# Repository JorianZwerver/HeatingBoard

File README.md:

# Heating Board PCB

PCB for MOD11 project. Measures current of four channels and can PWM each channel using a PMOS circuit. 

Schematic: [Schematic](Exports/HeatingBoard.pdf) \
Test results: [Results](Testing/2025_03_31_Test_Plan_Heating_Board_Execution.pdf) \
Test code for Arduino Uno: [Code](Testing/test_code.ino)

## Implementation

The board has 5 connectors:

| Connector ID | Description |
| ------------ | ----------- |
| J1 | Battery connector, is used for power. |
| J2 | Input interface for control, has a PWM pin for each group and the input for the 3V3 power. |
| J3 | I2C connector, contains SDA, SCL and GND. **However, the GND pin is broken and does not work.** |
| J4 | I2C connector, contains SDA, SCL and GND. |
| J5 | Output to the heating sleeve. Has four outputs and a GND that power the sleeve. |

### Current sensors

The current sensors communicate over the I2C bus. They need 3V3 power, but not battery power. The addresses are stated below:

| Channel number | Address (HEX) | Address (BIN) | Shunt resistor value (mOhm) |
| -------------- | ------------- | ------------- | --------------------- |
| 1 | 0x45 | 1000101 | 101   |
| 2 | 0x44 | 1000100 | 101.2 |
| 3 | 0x41 | 1000001 | 100.5 |
| 4 | 0x40 | 1000000 | 100.6 |

The datasheet can be found using this [link](https://www.ti.com/lit/ds/symlink/ina219.pdf?ts=1744040891714&ref_url=https%253A%252F%252Fwww.ti.com%252Fproduct%252FINA219). We have tested the current sensors in combination with a small load and encountered problems with the PWM, since the current sensor would sometimes measure the full current and sometimes zero current. To solve this, we increased the sample size and PWM frequency. This does mean that the sensor takes ~ 70 ms to get new data. We recommend the following settings:

- 12 bit shunt resolution
- 128 samples per measurement
- 2.5 kHz PWM frequency

We have found pretty accurate results using these settings, only deviating a couple of mW from the power supply. The testing code can be found [here](Testing/test_code.ino). The resistor values of the current shunts are shown in the table with the addresses for the current sensors.

### MOSFETs

During testing, we found that the duty cycle of the output voltage starts deviating from the input duty cycle for higher PWM frequencies. We have tested this for frequencies of 2.5, 5 and 10 kHz and we recommend 2.5 kHz. All results can be found in the [test report](Testing/2025_03_31_Test_Plan_Heating_Board_Execution.pdf).

## 3D Images

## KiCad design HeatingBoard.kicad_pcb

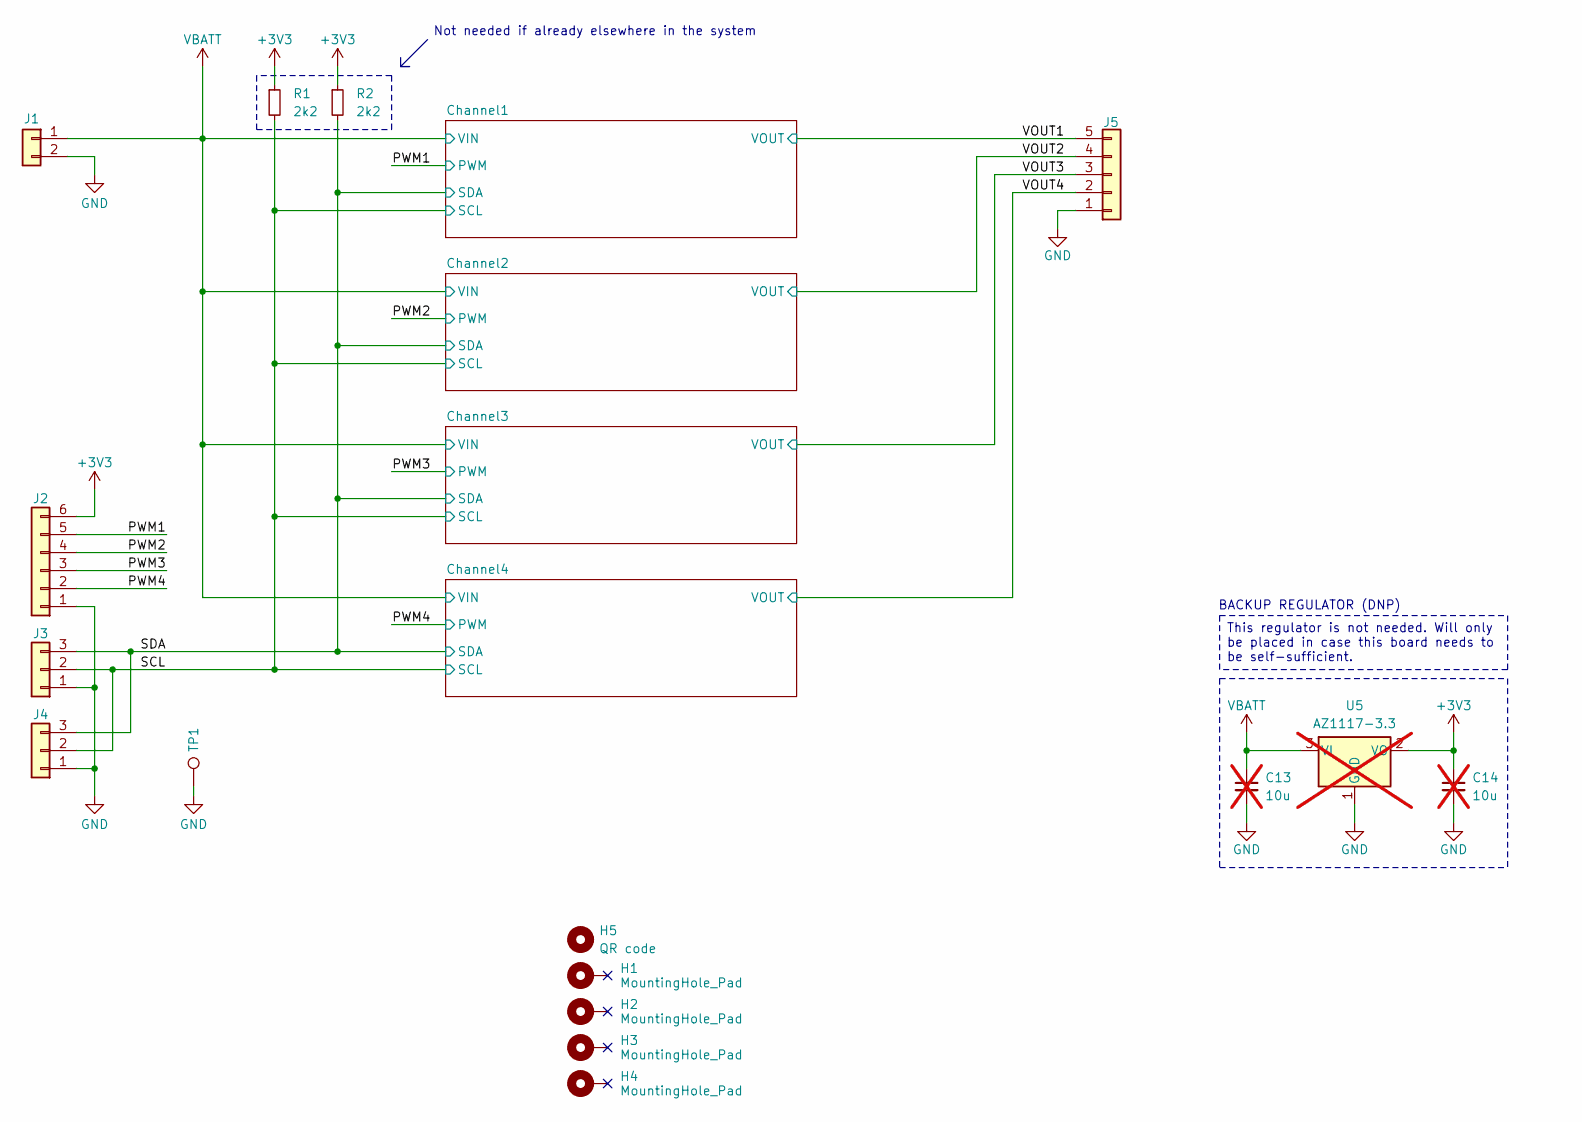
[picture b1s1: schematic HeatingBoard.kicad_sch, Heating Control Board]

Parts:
C13, C14: 10u; C_0805_2012Metric_Pad1.18x1.45mm_HandSolder; not fitted
H1, H2, H3, H4: MountingHole_Pad; MountingHole_3.2mm_M3_Pad
H5: QR code; QRcode
J1: Conn_01x02; PHOENIX_1935161
J2: Conn_01x06; PHOENIX_1935200
J3, J4: Conn_01x03; PHOENIX_1935174
J5: Conn_01x05; PHOENIX_1935190
R1, R2: 2k2; R_0603_1608Metric_Pad0.98x0.95mm_HandSolder
TP1: TestPoint; TestPoint_Plated_Hole_D5.0mm
U5: AZ1117-3.3; TO-220-3_Vertical; not fitted

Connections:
+3V3: C14.1, J2.6, R1.1, R2.1, U5.2 (VO); also elsewhere on the board
/PWM1: J2.5; also elsewhere on the board
/PWM2: J2.4; also elsewhere on the board
/PWM3: J2.3; also elsewhere on the board
/PWM4: J2.2; also elsewhere on the board
/SCL: J3.2, J4.2, R1.2; also elsewhere on the board
/SDA: J3.3, J4.3, R2.2; also elsewhere on the board
/VOUT1: J5.5; also elsewhere on the board
/VOUT2: J5.4; also elsewhere on the board
/VOUT3: J5.3; also elsewhere on the board
/VOUT4: J5.2; also elsewhere on the board
GND: C13.2, C14.2, J1.2, J2.1, J3.1, J4.1, J5.1, TP1.1, U5.1 (GND); also elsewhere on the board
VBATT: C13.1, J1.1, U5.3 (VI); also elsewhere on the board

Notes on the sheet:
BACKUP REGULATOR (DNP)
Not needed if already elsewhere in the system
This regulator is not needed. Will only be placed in case this board needs to be self-sufficient.

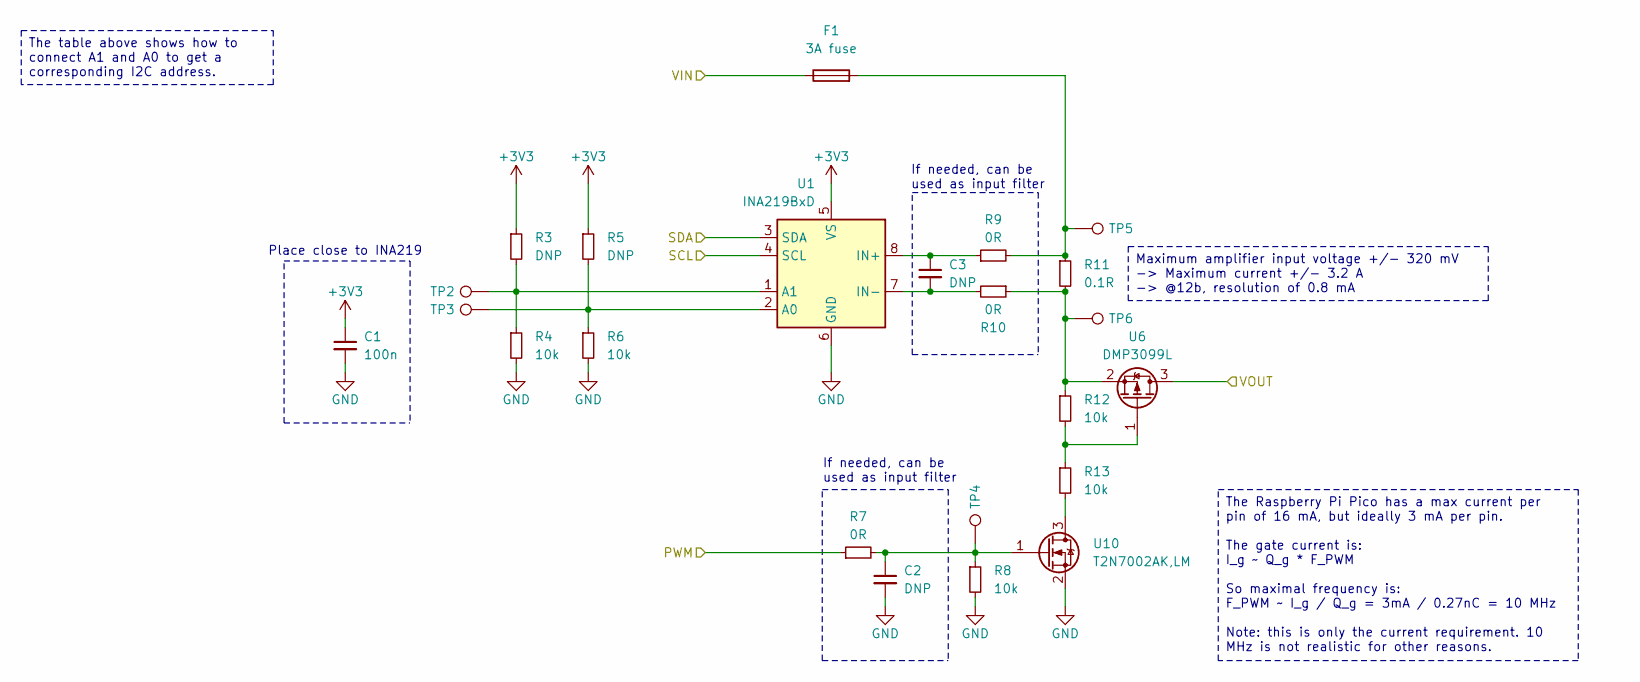
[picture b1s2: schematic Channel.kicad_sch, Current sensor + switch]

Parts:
C1: 100n; C_0603_1608Metric_Pad1.08x0.95mm_HandSolder
C2, C3: DNP; C_0603_1608Metric_Pad1.08x0.95mm_HandSolder
F1: 3A fuse; FUSE_0PTF0078P_LTF
R3, R5: DNP; R_0603_1608Metric_Pad0.98x0.95mm_HandSolder
R4, R6, R8, R12, R13: 10k; R_0603_1608Metric_Pad0.98x0.95mm_HandSolder
R7, R9, R10: 0R; R_0603_1608Metric_Pad0.98x0.95mm_HandSolder
R11: 0.1R; R_1206_3216Metric_Pad1.30x1.75mm_HandSolder
TP2, TP3, TP4, TP5, TP6: TestPoint; TestPoint_THTPad_1.0x1.0mm_Drill0.5mm
U1: INA219BxD; SOIC-8_3.9x4.9mm_P1.27mm
U6: DMP3099L; SOT-23
U10: T2N7002AK,LM; SOT-23

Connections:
+3V3: C1.1, R3.1, R5.1, U1.5 (VS); also elsewhere on the board
/PWM1: R7.1; also elsewhere on the board
/SCL: U1.4 (SCL); also elsewhere on the board
/SDA: U1.3 (SDA); also elsewhere on the board
/VOUT1: U6.3; also elsewhere on the board
GND: C1.2, C2.2, R4.2, R6.2, R8.2, U1.6 (GND), U10.2; also elsewhere on the board
unnamed: C2.1, R7.2, R8.1, TP4.1, U10.1
unnamed: F1.2, R9.2, R11.1, TP5.1
unnamed: R10.1, R11.2, R12.1, TP6.1, U6.2
unnamed: R12.2, R13.1, U6.1
unnamed: R13.2, U10.3
unnamed: R5.2, R6.1, TP3.1, U1.2 (A0)
unnamed: R3.2, R4.1, TP2.1, U1.1 (A1)
unnamed: C3.1, R9.1, U1.8 (IN+)
unnamed: C3.2, R10.2, U1.7 (IN-)
VBATT: F1.1; also elsewhere on the board

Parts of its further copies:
C4, C7, C10: 100n; C_0603_1608Metric_Pad1.08x0.95mm_HandSolder
C5, C6, C8, C9, C11, C12: DNP; C_0603_1608Metric_Pad1.08x0.95mm_HandSolder
F2, F3, F4: 3A fuse; FUSE_0PTF0078P_LTF
R14, R16, R25, R27, R36, R38: DNP; R_0603_1608Metric_Pad0.98x0.95mm_HandSolder
R15, R17, R19, R23, R24, R26, R28, R30, R34, R35, R37, R39, R41, R45, R46: 10k; R_0603_1608Metric_Pad0.98x0.95mm_HandSolder
R18, R20, R21, R29, R31, R32, R40, R42, R43: 0R; R_0603_1608Metric_Pad0.98x0.95mm_HandSolder
R22, R33, R44: 0.1R; R_1206_3216Metric_Pad1.30x1.75mm_HandSolder
TP7, TP8, TP9, TP10, TP11, TP12, TP13, TP14, TP15, TP16, TP17, TP18, TP19, TP20, TP21: TestPoint; TestPoint_THTPad_1.0x1.0mm_Drill0.5mm
U2, U3, U4: INA219BxD; SOIC-8_3.9x4.9mm_P1.27mm
U7, U8, U9: DMP3099L; SOT-23
U11, U12, U13: T2N7002AK,LM; SOT-23

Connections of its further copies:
+3V3: C4.1, C7.1, C10.1, R14.1, R16.1, R25.1, R27.1, R36.1, R38.1, U2.5 (VS), U3.5 (VS), U4.5 (VS); also elsewhere on the board
/PWM2: R18.1; also elsewhere on the board
/PWM3: R29.1; also elsewhere on the board
/PWM4: R40.1; also elsewhere on the board
/SCL: U2.4 (SCL), U3.4 (SCL), U4.4 (SCL); also elsewhere on the board
/SDA: U2.3 (SDA), U3.3 (SDA), U4.3 (SDA); also elsewhere on the board
/VOUT2: U7.3; also elsewhere on the board
/VOUT3: U8.3; also elsewhere on the board
/VOUT4: U9.3; also elsewhere on the board
GND: C4.2, C5.2, C7.2, C8.2, C10.2, C11.2, R15.2, R17.2, R19.2, R26.2, R28.2, R30.2, R37.2, R39.2, R41.2, U2.6 (GND), U3.6 (GND), U4.6 (GND), U11.2, U12.2, U13.2; also elsewhere on the board
unnamed: C5.1, R18.2, R19.1, TP9.1, U11.1
unnamed: C8.1, R29.2, R30.1, TP14.1, U12.1
unnamed: C11.1, R40.2, R41.1, TP19.1, U13.1
unnamed: F2.2, R20.2, R22.1, TP10.1
unnamed: F3.2, R31.2, R33.1, TP15.1
unnamed: F4.2, R42.2, R44.1, TP20.1
unnamed: R21.1, R22.2, R23.1, TP11.1, U7.2
unnamed: R23.2, R24.1, U7.1
unnamed: R24.2, U11.3
unnamed: R32.1, R33.2, R34.1, TP16.1, U8.2
unnamed: R34.2, R35.1, U8.1
unnamed: R35.2, U12.3
unnamed: R43.1, R44.2, R45.1, TP21.1, U9.2
unnamed: R45.2, R46.1, U9.1
unnamed: R46.2, U13.3
unnamed: R16.2, R17.1, TP8.1, U2.2 (A0)
unnamed: R14.2, R15.1, TP7.1, U2.1 (A1)
unnamed: C6.1, R20.1, U2.8 (IN+)
unnamed: C6.2, R21.2, U2.7 (IN-)
unnamed: R27.2, R28.1, TP13.1, U3.2 (A0)
unnamed: R25.2, R26.1, TP12.1, U3.1 (A1)
unnamed: C9.1, R31.1, U3.8 (IN+)
unnamed: C9.2, R32.2, U3.7 (IN-)
unnamed: R38.2, R39.1, TP18.1, U4.2 (A0)
unnamed: R36.2, R37.1, TP17.1, U4.1 (A1)
unnamed: C12.1, R42.1, U4.8 (IN+)
unnamed: C12.2, R43.2, U4.7 (IN-)
VBATT: F2.1, F3.1, F4.1; also elsewhere on the board

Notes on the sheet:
Place close to INA219
If needed, can be used as input filter
Maximum amplifier input voltage +/- 320 mV -> Maximum current +/- 3.2 A -> @12b, resolution of 0.8 mA
The Raspberry Pi Pico has a max current per pin of 16 mA, but ideally 3 mA per pin. The gate current is: I_g ~ Q_g * F_PWM So maximal frequency is: F_PWM ~ I_g / Q_g = 3mA / 0.27nC = 10 MHz Note: this is only the current requirement. 10 MHz is not realistic for other reasons.
The table above shows how to connect A1 and A0 to get a corresponding I2C address.

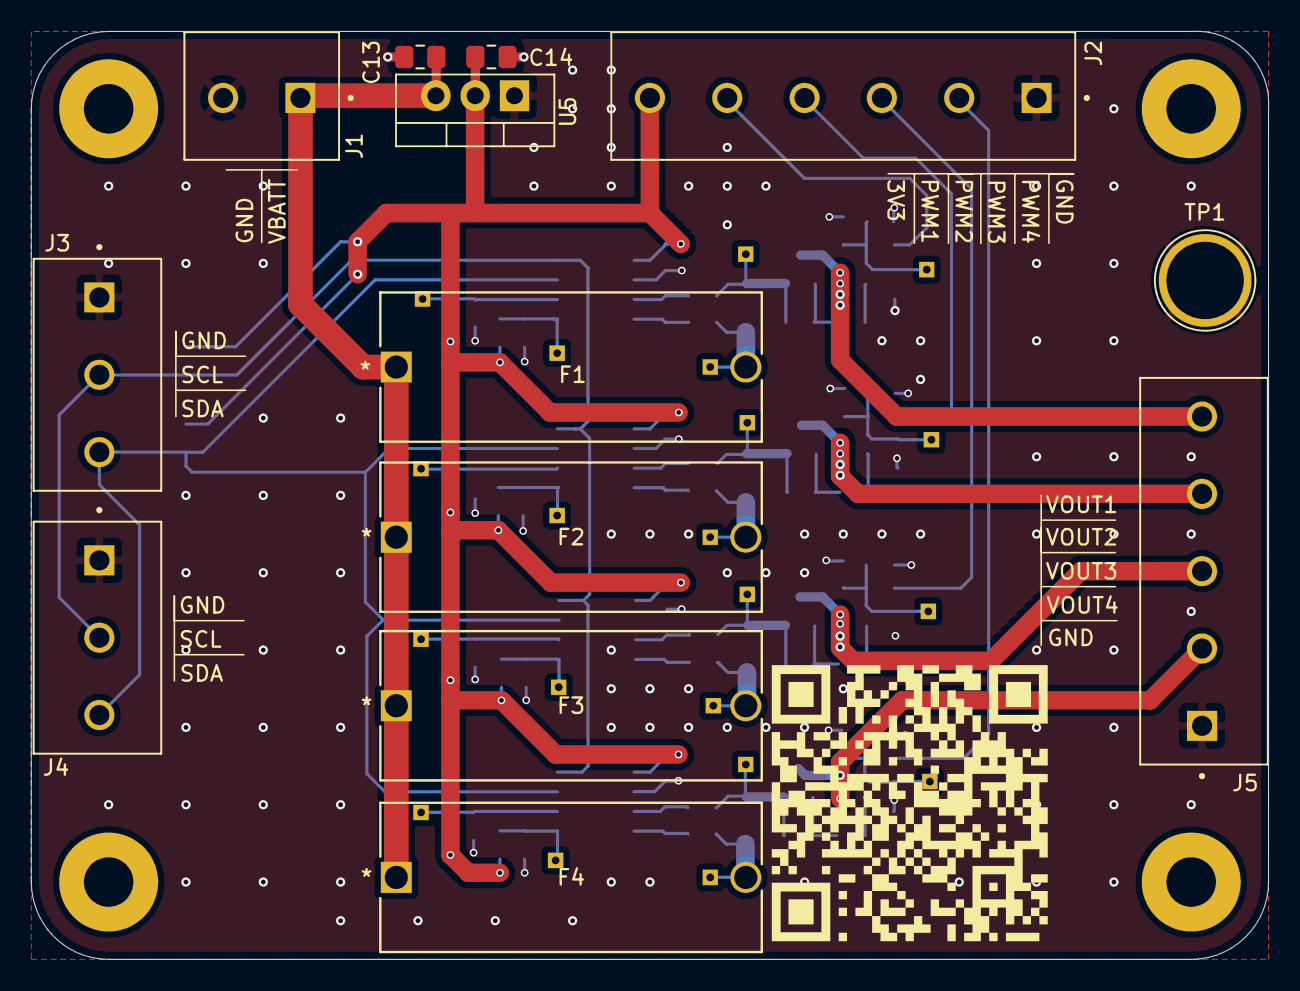
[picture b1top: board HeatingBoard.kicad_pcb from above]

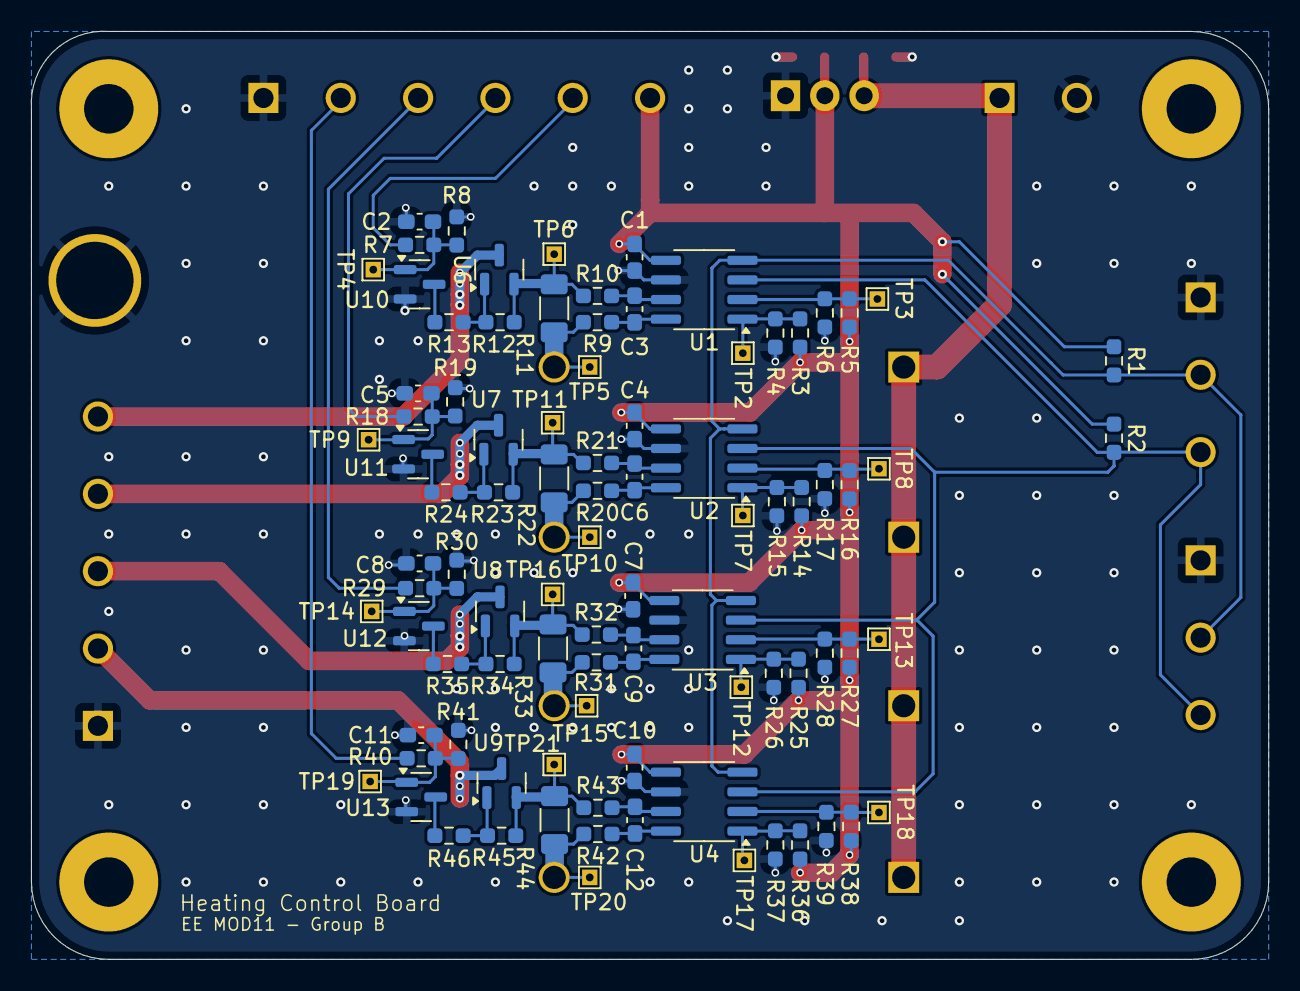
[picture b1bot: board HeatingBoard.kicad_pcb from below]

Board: 2 copper layers, 80.0 x 60.0 mm, 108 parts (90 on the bottom side), 49 nets.

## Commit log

2025-03-20 Save issues
2025-03-23 Finished PCB
2025-03-24 Added 3D models
2025-03-24 Added QR code and images
2025-03-25 Full review
    Notes in README. TLDR: MOSFET footprint pinouts are incorrect
2025-03-25 Fixed review comments
2025-04-08 Updated readme and addes test results
2025-04-09 Changed max current in test code
